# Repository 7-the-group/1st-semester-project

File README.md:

# Group 7 semester project

# How to start

All the necessary parts are in Product folder. In Product/PCB there are two zip files for PCB manufacturing one is for PCB with the Arduino and the other one is for PCB with buttons. When PCBs are printed and assembled refer to the documentation appendices for correct connection.

In Product/Models folder you can find .stl files for control panel casing and base. We also created casings for potentiometers and buttons however those serve only esthetic function. Next there is .dxf file, which contains walls model for laser cutter.

Finally in Product/Software folder is PlatformIO project with all the necessary code, just upload it to Arduino.

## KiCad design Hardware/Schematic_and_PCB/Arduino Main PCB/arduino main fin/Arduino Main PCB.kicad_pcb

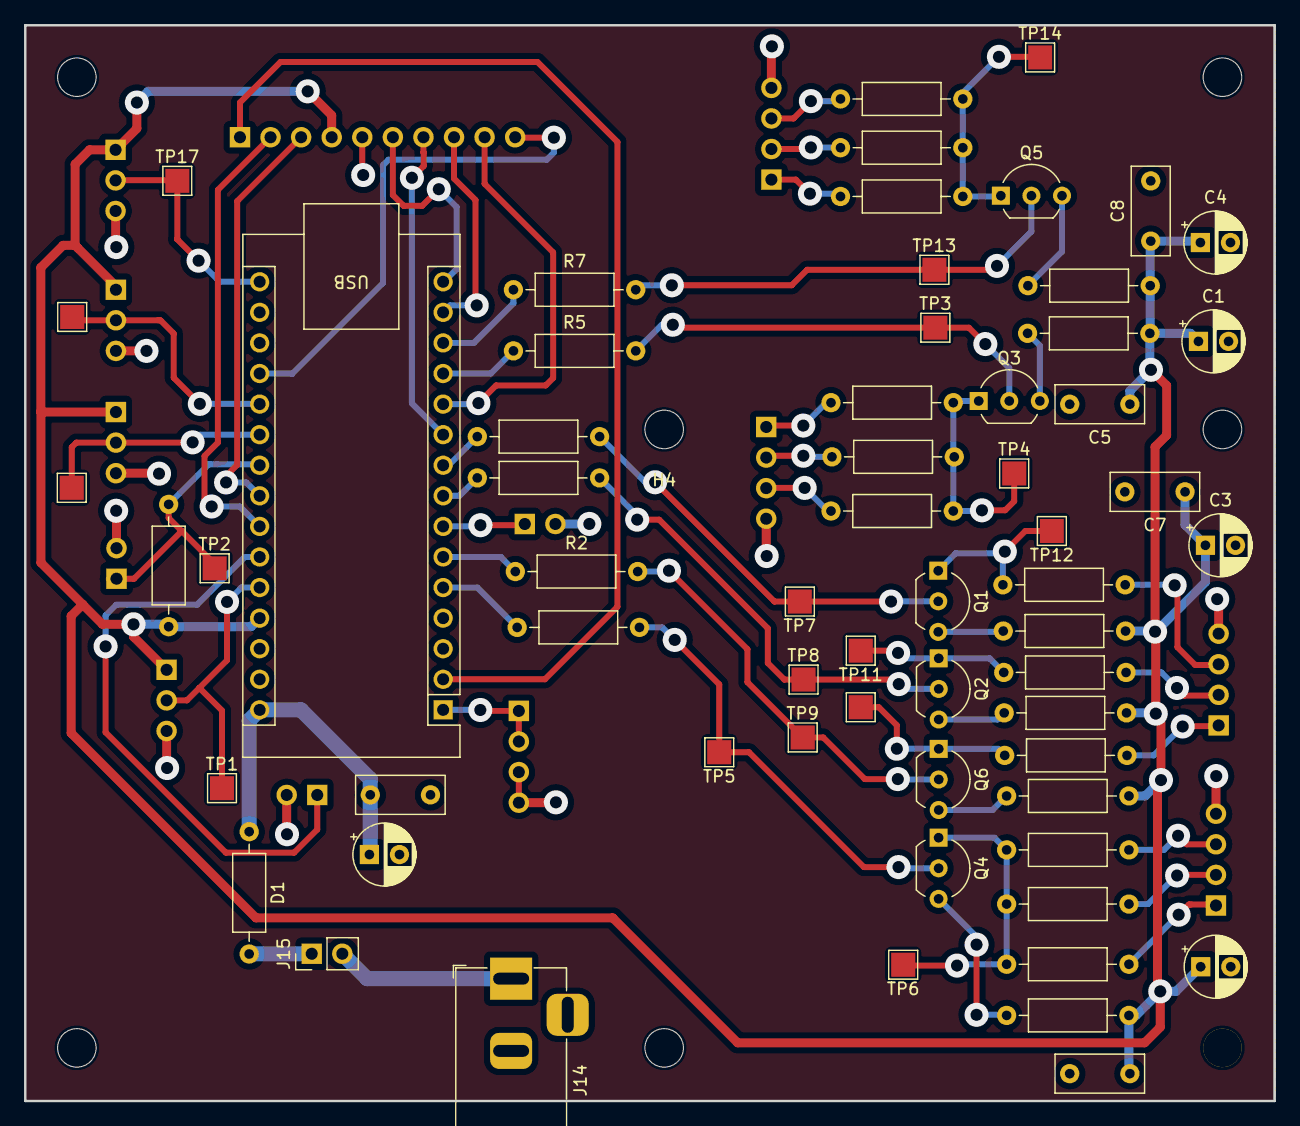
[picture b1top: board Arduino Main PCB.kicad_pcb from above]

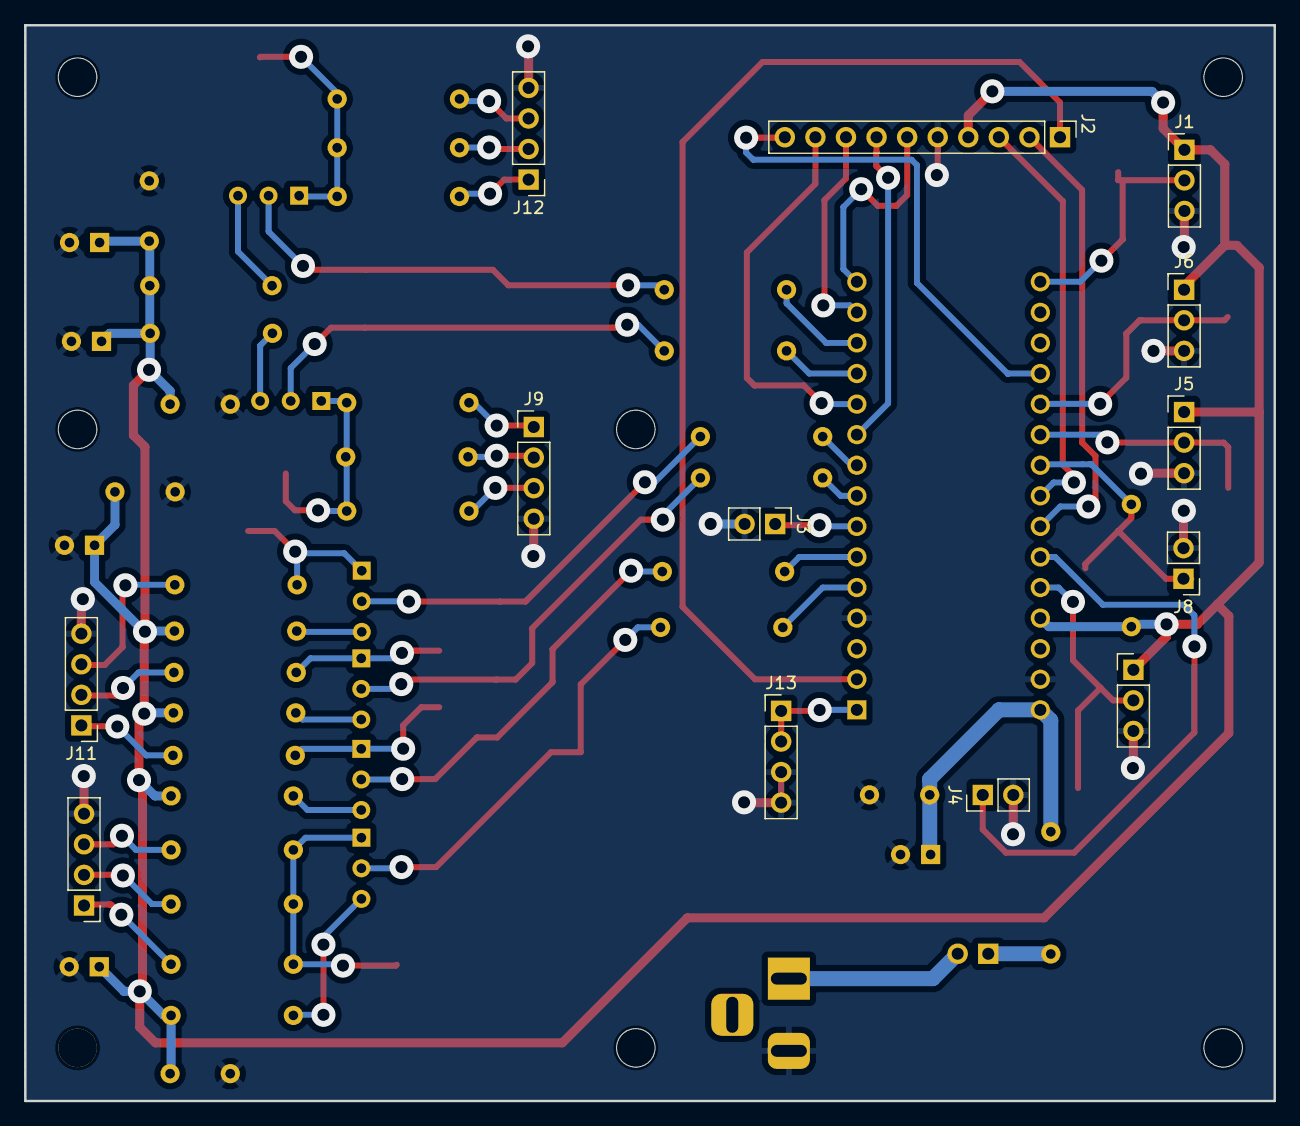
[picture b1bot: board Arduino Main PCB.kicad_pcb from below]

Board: 2 copper layers, 103.8 x 89.4 mm, 82 parts (13 on the bottom side), 57 nets.

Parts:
A1: Arduino_Nano_Every; Arduino_Nano
C1, C2, C3, C4, C10: 4.7mu; CP_Radial_D5.0mm_P2.50mm
C5, C6, C7, C8, C9: 100n; C_Rect_L7.2mm_W3.0mm_P5.00mm_FKS2_FKP2_MKS2_MKP2
D1: D; R_Axial_DIN0207_L6.3mm_D2.5mm_P10.16mm_Horizontal
H1, H2, H3, H4, H5, H6, H7: MountingHole; MountingHole_3.2mm_M3
J1: PIR_sensor; PinHeader_1x03_P2.54mm_Vertical
J2: Control_Panel; PinHeader_1x10_P2.54mm_Vertical
J3: Buttons_Room_3; PinHeader_1x02_P2.54mm_Vertical
J4: Buttons_Room_1; PinHeader_1x02_P2.54mm_Vertical
J5: Pot_Room_3.1; PinHeader_1x03_P2.54mm_Vertical
J6: Pot_Room_1; PinHeader_1x03_P2.54mm_Vertical
J7: Pot_Room_3.2; PinHeader_1x03_P2.54mm_Vertical
J8: LDR_Door; PinHeader_1x02_P2.54mm_Vertical
J9: LED_Room_1; PinHeader_1x04_P2.54mm_Vertical
J10: LED_Room_2; PinHeader_1x04_P2.54mm_Vertical
J11: LED_Room_3; PinHeader_1x04_P2.54mm_Vertical
J12: LED_DOOR; PinHeader_1x04_P2.54mm_Vertical
J13: Buttons_Room_2; PinHeader_1x04_P2.54mm_Vertical
J14: Barrel_Jack; BarrelJack_Horizontal
J15: Power switch; PinHeader_1x02_P2.54mm_Vertical
Q1, Q2, Q3, Q4, Q5, Q6: BC557; TO-92_Inline_Wide
R1, R8, R9, R10, R23, R24, R25: 80; R_Axial_DIN0207_L6.3mm_D2.5mm_P10.16mm_Horizontal
R2, R3, R4: 82k; R_Axial_DIN0207_L6.3mm_D2.5mm_P10.16mm_Horizontal
R5, R6, R7: 1k; R_Axial_DIN0207_L6.3mm_D2.5mm_P10.16mm_Horizontal
R11, R14, R20: 650; R_Axial_DIN0207_L6.3mm_D2.5mm_P10.16mm_Horizontal
R12, R13, R15, R16, R21, R22: 450; R_Axial_DIN0207_L6.3mm_D2.5mm_P10.16mm_Horizontal
R17: 330; R_Axial_DIN0207_L6.3mm_D2.5mm_P10.16mm_Horizontal
R18, R19: 220; R_Axial_DIN0207_L6.3mm_D2.5mm_P10.16mm_Horizontal
TP1, TP2, TP3, TP4, TP5, TP6, TP7, TP8, TP9, TP10, TP11, TP12, TP13, TP14, TP15, TP16, TP17: TestPoint; TestPoint_Pad_2.0x2.0mm

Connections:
+5V: A1.27 (+5V), C1.1, C2.1, C3.1, C4.1, C5.1, C6.1, C7.1, C8.1, J1.1, J2.4, J5.1, J6.1, J7.1, R1.1, R8.1, R9.1, R10.1, R23.1, R24.1, R25.1
+9V: A1.30 (VIN), C9.1, C10.1, D1.1 (K)
GND: A1.4 (GND), A1.29 (GND), C1.2, C2.2, C3.2, C4.2, C5.2, C6.2, C7.2, C8.2, C9.2, C10.2, J1.3, J2.5, J3.2, J4.2, J5.3, J6.3, J7.3, J8.2, J9.4, J10.4, J11.4, J12.4, J13.3, J13.4, J14.2
unnamed: A1.20 (A1), J6.2, TP15.1
unnamed: A1.21 (A2), J5.2, TP16.1
unnamed: A1.22 (A3), J8.1, R25.2, TP2.1
unnamed: A1.25 (A6), J4.1
unnamed: A1.26 (A7), J7.2, TP1.1
unnamed: A1.1 (D0), J13.1, J13.2
unnamed: A1.7 (D4), J3.1
unnamed: A1.16 (D13), J1.2, TP17.1
unnamed: D1.2 (A), J15.1
unnamed: J9.1, R11.2
unnamed: J9.2, R12.2
unnamed: J9.3, R13.2
unnamed: J10.1, R14.2
unnamed: J10.2, R15.2
unnamed: J10.3, R16.2
unnamed: J11.1, R17.2
unnamed: J11.2, R18.2
unnamed: J11.3, R19.2
unnamed: J12.1, R20.2
unnamed: J12.2, R21.2
unnamed: J12.3, R22.2
unnamed: J14.1, J15.2
unnamed: Q1.2 (B), R4.2, TP7.1
unnamed: Q1.1 (C), R19.1, TP12.1
unnamed: Q1.3 (E), R1.2
unnamed: Q2.2 (B), R3.2, TP8.1
unnamed: Q2.1 (C), R18.1, TP11.1
unnamed: Q2.3 (E), R23.2
unnamed: Q3.2 (B), R5.2, TP3.1
unnamed: Q3.1 (C), R11.1, R12.1, R13.1, TP4.1
unnamed: Q3.3 (E), R8.2
unnamed: Q4.2 (B), R6.2, TP5.1
unnamed: Q4.1 (C), R14.1, R15.1, R16.1, TP6.1
unnamed: Q4.3 (E), R9.2
unnamed: Q5.2 (B), R7.2, TP13.1
unnamed: Q5.1 (C), R20.1, R21.1, R22.1, TP14.1
unnamed: Q5.3 (E), R10.2
unnamed: Q6.2 (B), R2.2, TP9.1
unnamed: Q6.1 (C), R17.1, TP10.1
unnamed: Q6.3 (E), R24.2
blue led room 3: A1.9 (D6), R4.1
button back: A1.15 (D12), J2.6
button down: A1.11 (D8), J2.9
button ok: A1.14 (D11), J2.8
button sleep: A1.2 (D1), J2.1
button up: A1.10 (D7), J2.7
control panel pot: A1.19 (A0), J2.10
green led room 3: A1.8 (D5), R3.1
lcd SCL: A1.24 (SCL/A5), J2.2
lcd SDA: A1.23 (SDA/A4), J2.3
led door: A1.13 (D10), R7.1
led room 1: A1.12 (D9), R5.1
led room 2: A1.5 (D2), R6.1
red led room 3: A1.6 (D3), R2.1

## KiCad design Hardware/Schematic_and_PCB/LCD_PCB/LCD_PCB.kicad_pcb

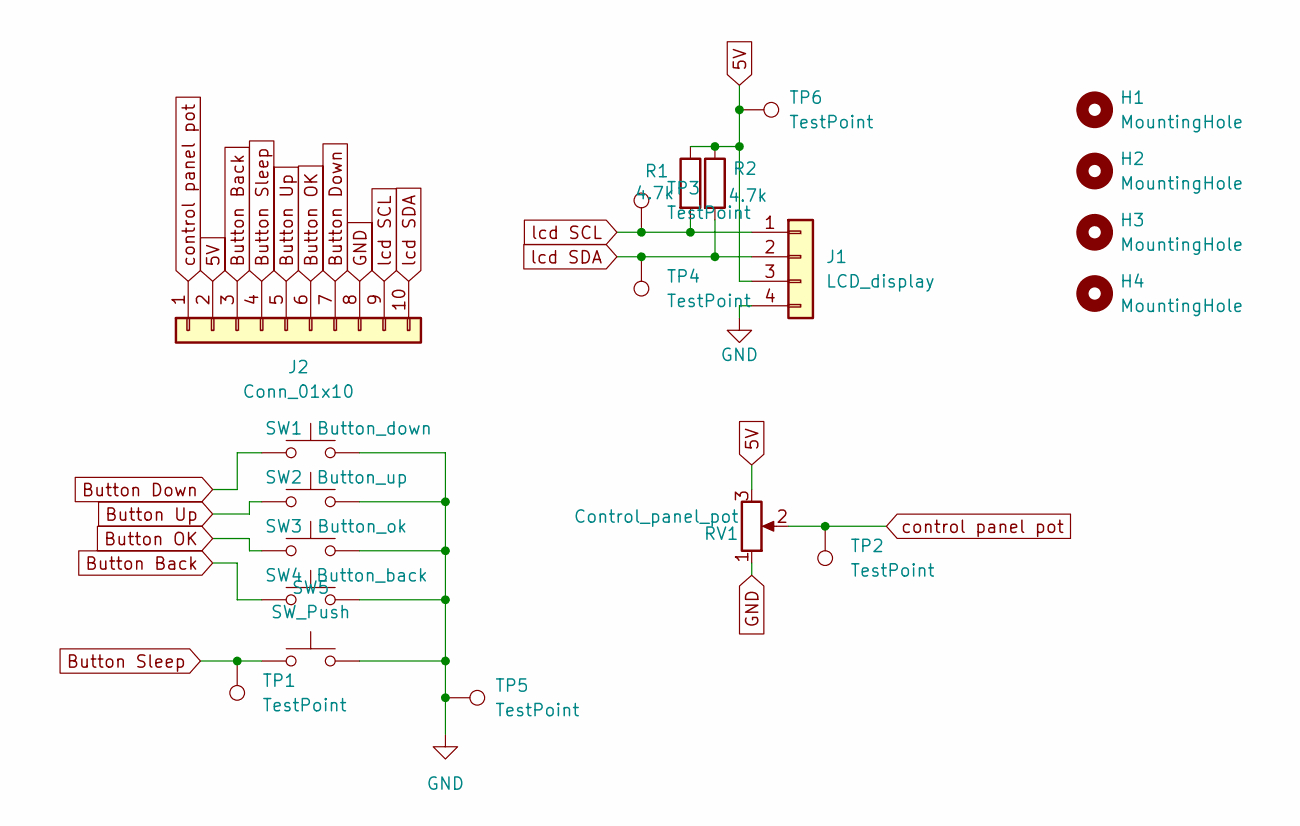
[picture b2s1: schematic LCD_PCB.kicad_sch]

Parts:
H1, H2, H3, H4: MountingHole; MountingHole_3.2mm_M3
J1: LCD_display; PinHeader_1x04_P2.54mm_Vertical
J2: Conn_01x10; PinHeader_1x10_P2.54mm_Vertical
R1, R2: 4.7k; R_Axial_DIN0207_L6.3mm_D2.5mm_P7.62mm_Horizontal
RV1: Control_panel_pot; PDB182-K-Potentiometer-Horizontal
SW1: Button_down; SW_PUSH_6mm_H5mm
SW2: Button_up; SW_PUSH_6mm_H5mm
SW3: Button_ok; SW_PUSH_6mm_H5mm
SW4: Button_back; SW_PUSH_6mm_H5mm
SW5: SW_Push; SW_PUSH_6mm_H5mm
TP1, TP2, TP3, TP4, TP5, TP6: TestPoint; TestPoint_Pad_1.5x1.5mm

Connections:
5V: J1.3, J2.2, R1.1, R2.1, RV1.3, TP6.1
Button Back: J2.3, SW4.1
Button Down: J2.7, SW1.1
Button OK: J2.6, SW3.1
Button Sleep: J2.4, SW5.1, TP1.1
Button Up: J2.5, SW2.1
GND: J1.4, J2.8, RV1.1, SW1.2, SW2.2, SW3.2, SW4.2, SW5.2, TP5.1
control panel pot: J2.1, RV1.2, TP2.1
lcd SCL: J1.1, J2.9, R1.2, TP3.1
lcd SDA: J1.2, J2.10, R2.2, TP4.1

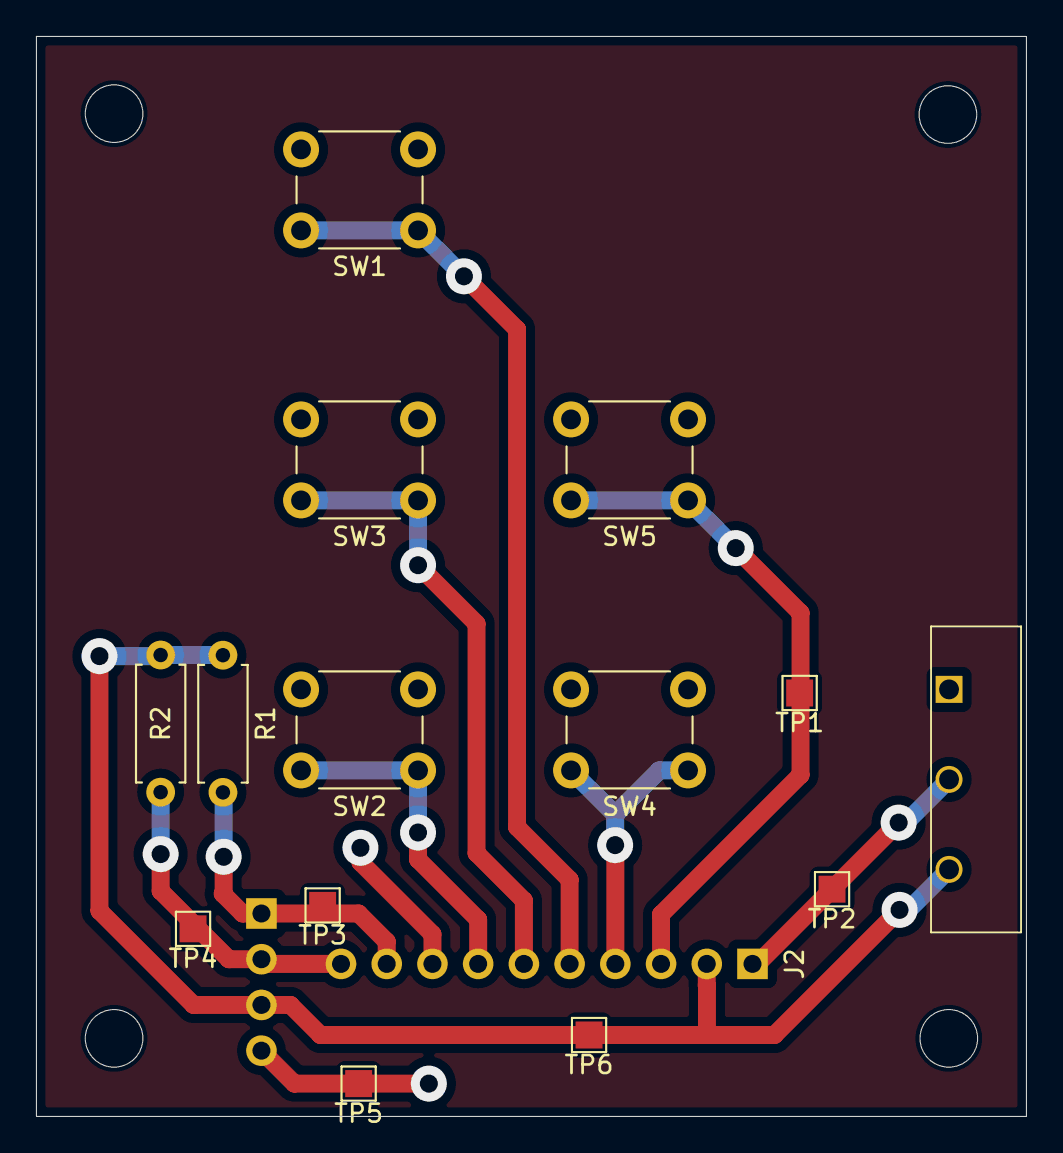
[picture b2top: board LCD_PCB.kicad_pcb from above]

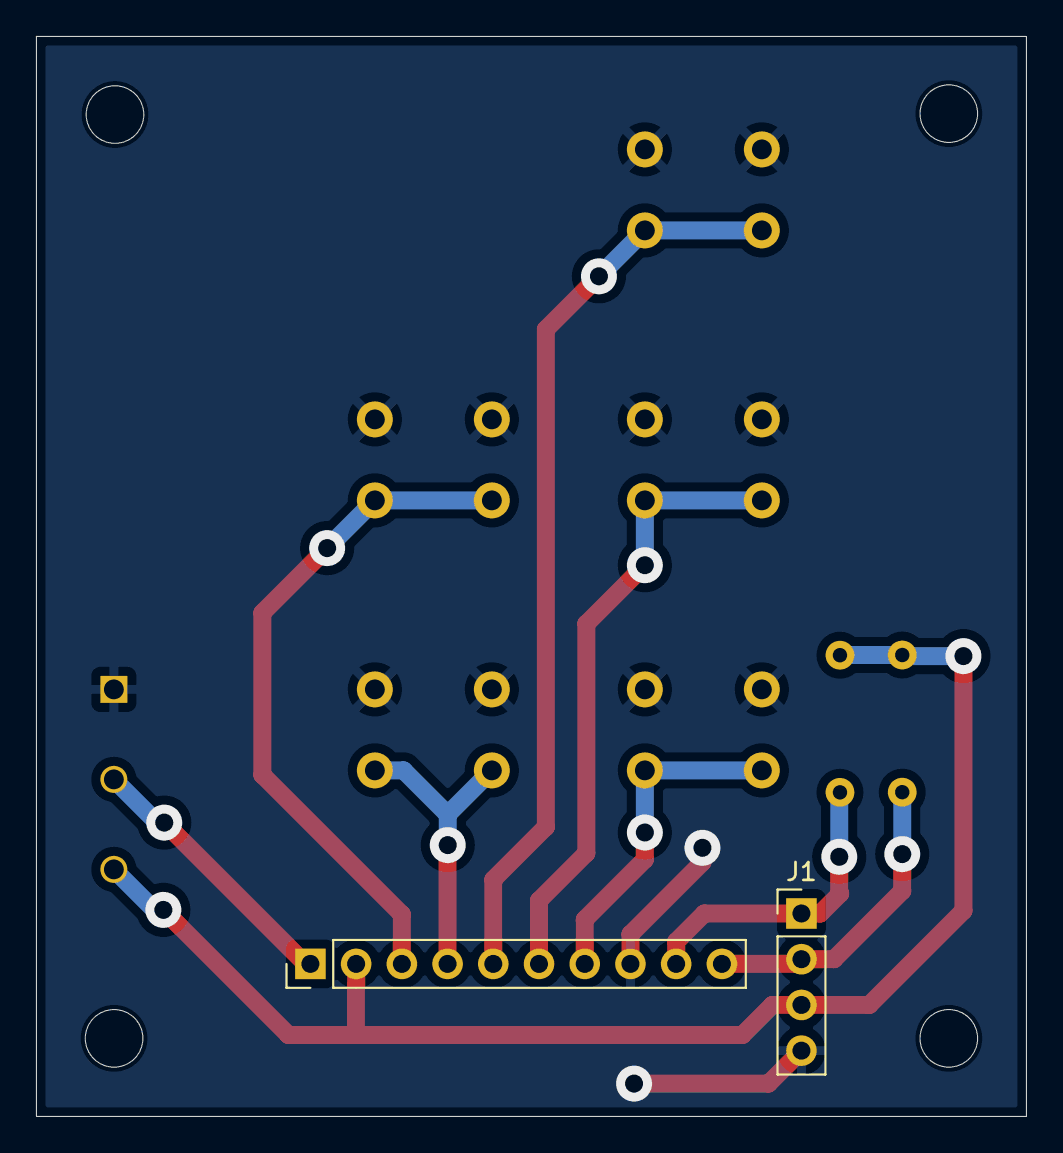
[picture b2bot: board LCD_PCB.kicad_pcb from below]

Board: 2 copper layers, 55.0 x 60.0 mm, 20 parts (2 on the bottom side), 10 nets.

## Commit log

2024-09-19 Initial commit.
2024-09-19 Update 19.9.2024.md
    Remove everything.
2024-09-20 Create test.txt
    This a test commit only for demonstration.
2024-09-20 Add some learning materials for GitHub.
2024-09-21 Finish learning materials for GitHub.
2024-09-21 Add notes for 3D modeling.
2024-09-21 Add notes for PCB design.
2024-09-21 Add Atmel-7810-Automotive-Microcontrollers-ATmega328P_Datasheet.pdf.
2024-09-21 Add notes for Arduino.
2024-09-21 Format CODE_OF_CONDUCT.md
2024-09-21 Add files via upload
    Team color combination
2024-09-25 revert
2024-09-25 Add Visual studio Code project.
2024-09-25 Add project description.
2024-09-26 Added folder for organization
    We don't want to have mess here
2024-09-26 Move the chart to project assignments folder for organization
2024-09-26 Update assignment
2024-09-26 Created folder for team stuff
2024-09-26 Clean up
2024-09-26 Move to new folder - clean-up
2024-09-26 Move to separate folder
2024-09-26 Separate folder for the files from the meeting 26.09.2024
2024-09-26 Moved the file here - clean-up
2024-09-26 Rename LCD_sketch.jpg to LCD/LCD_sketch.jpg
2024-09-26 links of diodes to choose from
2024-09-26 Add project for visual studio.
2024-09-26 Remove test.txt.
2024-09-26 Move LCD to hardware folder.
2024-09-30 Added website of model for RGB LED
2024-09-30 Added RGB LED model
2024-09-30 RGB LED datasheet
2024-10-06 Added simulation folder
2024-10-07 Add list of components to buy.
2024-10-07 Move components.xlsx to meetings folder.
2024-10-08 Fix date on last meeting.
2024-10-09 Update components list.
2024-10-11 Add datasheets for arduino nano every and atmega4809.
2024-10-11 Update components list in hardware folder.
2024-10-11 Add Used pins.md.
2024-10-11 Add KiCad projects for individual rooms, door and control panel.
2024-10-11 Add schematic for room 2.
2024-10-12 Rename meeting_board.jpg to meeting_board.jpg
2024-10-16 Room 3 schematic
2024-10-16 Update room 3 schematic
2024-10-17 Update room 2 schematic.
2024-10-17 Create Scematic for Control Panel
2024-10-17 Added custom Arduino every Symbol
2024-10-17 Change transistors in room 3 schematic
2024-10-17 Add smart home pinout in kicad.
2024-10-19 Combine partial schematics into one.
2024-10-19 Remove some temp files.
2024-10-21 Move schematic and PCB design to schematic_and_PCB folder.
2024-10-21 Replace arduino nano every symbol with new symbol and add resistor values.
2024-10-21 Create folders for 3D design.
2024-10-21 Add notes for today's meeting.
2024-10-21 Add images for today's meeting.
2024-10-21 Change schematic as was agreed on a meeting, also change used pins.md.
2024-10-23 Create Button case V1.pdf
    Added button casing blueprint
2024-10-24 Add meeting notes
2024-10-27 Add floor 3D model.
2024-10-27 Update resistor values.
2024-10-28 Add transistor datasheet - BC557B
2024-10-28 Update room 3 with calculations
2024-10-29 Added the basic model of the walls
    Added the basic model of the walls
2024-10-29 updated version of the wall model with holes
2024-10-30 put windows on the walls model
2024-10-30 add project link
2024-10-30 Added links to model and drawing
2024-10-30 Old files deleted
2024-10-30 Update drawing
2024-10-30 Add new drawing
2024-10-31 Updated calculations
2024-10-31 Update smarthome schematic with calculations
2024-11-01 saved control panel schematic
2024-11-01 updated whole schematic with calculations
2024-11-01 Update LCD PCB
2024-11-01 Update PCB LCD
2024-11-01 Update Used pins.md
    Add ports
2024-11-01 Add room 2 header file.
2024-11-01 Update Used pins.md
    Fix ports
2024-11-01 Add program for room 2, not tested.
2024-11-01 Finish LCD PCB
2024-11-06 Update bunch of stuff
2024-11-08 Add datasheets for arduino nano.
2024-11-08 Add .gitignore.
2024-11-08 Remove Arduino nano every files.
2024-11-08 Remove datasheet for atmega 4809.
2024-11-08 Add floor and walls 3d model.
2024-11-08 Add code for room 3 unfinished.
2024-11-09 Update LCB PCB
2024-11-11 Finalize LCD PCB
2024-11-14 Uploaded Arduino Main PCB
2024-11-15 Fix bugs in adcpwm.c.
2024-11-15 Code update for room 3
2024-11-15 Update code for room 3
2024-11-15 Fix mistake
    Potentiometer 2 room 3 port from PD7 -> PC7
2024-11-17 Update room 3 code
2024-11-18 Update adcpwm library and room3
2024-11-21 LCD menu code
2024-11-21 arduino main fin saved as final pcb
2024-11-26 Add 3D design of walls with images.
2024-11-26 Update Used pins.md
    Add pin for PIR sensor.
2024-11-26 Update Used pins.md
    Add LED door pin.
2024-11-26 Door program implemented, not tested.
2024-11-26 Add get_light_door_status() function.
2024-11-26 Add manual override functionality in door program.
2024-11-28 Update code for menu
2024-11-29 Add menu_helper.h and menu_helper.c.
2024-11-29 created display.c
2024-12-02 Update menu code
2024-12-02 Update menu code
    get_current_elms() function added
2024-12-04 Update menu code
    Functions Move Up/Down, Select, Back & others
2024-12-04 Schematic of main PCB updated with Resistor values
2024-12-05 Some changes in ForLaserCutter.lrd.
2024-12-05 Added control_panel library
2024-12-05 Upload code for display
2024-12-05 Update display.h to receive Menu_element** instead of Menu_element*.
2024-12-05 updated arduino main schematic
2024-12-05 Update pinout order of LCD PCB
2024-12-05 empty commit.
2024-12-05 Add code for control_panel.
2024-12-06 Add code for room 1.
2024-12-06 Add file to gitignore.
2024-12-06 Add not saved code for room 1 from previous commit.
2024-12-06 Update .gitignore.
2024-12-06 Fixes after testing on hardware.
2024-12-06 Add list of things which works and which does not.
2024-12-06 Fixed menu code
2024-12-06 Try to fix code for room 3
2024-12-09 Create report template
2024-12-11 Use pointers to Menu_element instead of copying it.
2024-12-11 Little change in room_3.c.
2024-12-11 Do not control led using pins only pwm.
2024-12-11 Add implementation of a function for turning on an off light in room 3.
2024-12-11 Fix adcpwm.c.
2024-12-11 Fix pwm.
2024-12-11 Fix pwm 1.
2024-12-12 Remove Software .gitignore.
2024-12-12 Stop tracking of these annoying files.
2024-12-12 Fix menu navigation.
2024-12-14 Implement menu responsiveness to changes in rooms and overall navigation.
    - add ability to change values in menu
    - correctly display enum values in menu
    - change values in menu using buttons (not potentiometer)
    - change values in menu in real time
2024-12-14 Add control_panel.c implementation for menu.
2024-12-14 Add responsive implementation to control panel and menu.
2024-12-16 Fix rooms and door, programs for checking buttons and controling lights.
2024-12-16 Some value specifier rewrite.
2024-12-16 Add delay after buttons are pressed.
2024-12-18 made door code work
2024-12-18 Add pcb cover file for printing
2024-12-18 current room 3 test
2024-12-18 Try to fix pwm3_get_duty() function
2024-12-18 Fix pwm3_get_duty and add pwm1_get_duty.
2024-12-18 Fix pwm3_get_duty.
2024-12-18 Try to fix pwm3 get duty
2024-12-18 Remove room 3 pot 2 from menu.
2024-12-18 Change pin of buttons in room 2
2024-12-18 Fix pwm3_get_duty again.
2024-12-18 Remove room 3 pot 2 from functions_for_rooms.
2024-12-18 random
2024-12-19 Update main.c for testing.
2024-12-19 Add functions connecting door and control panel.
2024-12-19 Fix some bugs in functions_for_rooms.
2024-12-20 uploaded report of design choices and PCB
2024-12-20 Update to current pinout
2024-12-20 Add documentation folder.
2024-12-20 Remove documentation folder.
2024-12-21 Update
    Added figures and updated code
2024-12-21 Fix adcpwm.c hopefully final time.
2024-12-21 Fix door light status.
2024-12-21 Fix functions_for_rooms.c.
2024-12-21 Fix color changing in room 3.
2024-12-21 Fix hsv values in functions_for_rooms.c.
2024-12-21 Fix file element printing.
2024-12-21 Some changes in functions_for_rooms.c.
2024-12-21 Use fmod in functions_for_rooms.c.
2024-12-21 Remove modulo.
2024-12-21 Fix H in display change.
2024-12-21 Fix room 1 brightness.
2024-12-22 Add testing project for visual studio.
2024-12-22 Fix RGB to HSV conversion.
2024-12-22 Fix formatting in color.c.
2024-12-22 Replace int with float value in functions_for_rooms.c.
2024-12-22 Fix displaying of menu elements in display.c.
2024-12-22 Add ;
2024-12-22 Fix get_light_status_room_3 function.
2024-12-22 Fix getting light intensity room 1.
2024-12-22 Fix comments in control_panel.c.
2024-12-22 Add Visual Studio .gitignore.
2024-12-23 Fix get status of light in room 3.
2024-12-23 Fix room 3
2024-12-23 Fix room 1 light switching.
2024-12-23 Fix door light status setting
2024-12-23 New algorithm for converting rgb to hsv and vice versa.
2024-12-23 Attempt to fix room 3 light status change using control panel.
2024-12-23 Try to fix room 3 light status
2024-12-23 Room 3 fix.
2024-12-23 Remove HSV change functionality.
2024-12-23 Remove unused functions.
2024-12-23 Start report writing for software part.
2024-12-24 Updated the report of methodes
2024-12-24 Made the LCD PCB Schematic better readable
2024-12-27 updated report and added Figures
2024-12-27 Update software report.
2024-12-27 Rename functions_for_rooms to mediator.
2024-12-27 Add someDiagrams.drawio.
2024-12-27 Remove comments.
2024-12-27 Add figures to software report.
2024-12-27 updated Report to V2
2024-12-29 Make schematic more readable.
2024-12-29 Some changes related to pdf export.
2024-12-29 Update Methods chapter in ReportV2 and create PDFs which will be appendencies in final report.
2024-12-31 Add introduction to ReportV2.docx.
2025-01-01 Add appendices.
2025-01-01 Add button casing drawing to appendices.
2025-01-01 Add results chapter.
2025-01-01 Add references.
2025-01-01 Format title, add page numbers and header.
2025-01-01 Update abstract, add conclusion and RGBConverter library reference.
2025-01-01 Remove comments (old code)
2025-01-01 updated methode part of the report as V3
2025-01-01 Fix ReportV3 formatting.
2025-01-01 Added PCB cover file for printing
2025-01-01 Added calculations for report
2025-01-02 Update Introduction and bibliography in ReportV3
2025-01-02 Add Discussion, appendices and finalize report.
2025-01-02 Generate report-final.pdf.
2025-01-02 Add appendix references into text.
2025-01-02 Revert "Add appendix references into text."
    This reverts commit 3e2e4c01e940688dd59afcaaadaacaf16321aded.
2025-01-02 Added budget table
2025-01-02 Finalize report
2025-01-02 final version updated
2025-01-02 Add names and finalize report.
2025-01-02 Fix minor problems with appendices.
2025-01-10 Remove dragon pictures.
2025-01-10 Copy files to Product folder.
2025-01-10 Add documentation to Product folder.
